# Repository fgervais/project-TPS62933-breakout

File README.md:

#

## Generate gerbers for PCBWay

https://www.pcbway.com/blog/help_center/Generate_Gerber_file_from_Kicad.html

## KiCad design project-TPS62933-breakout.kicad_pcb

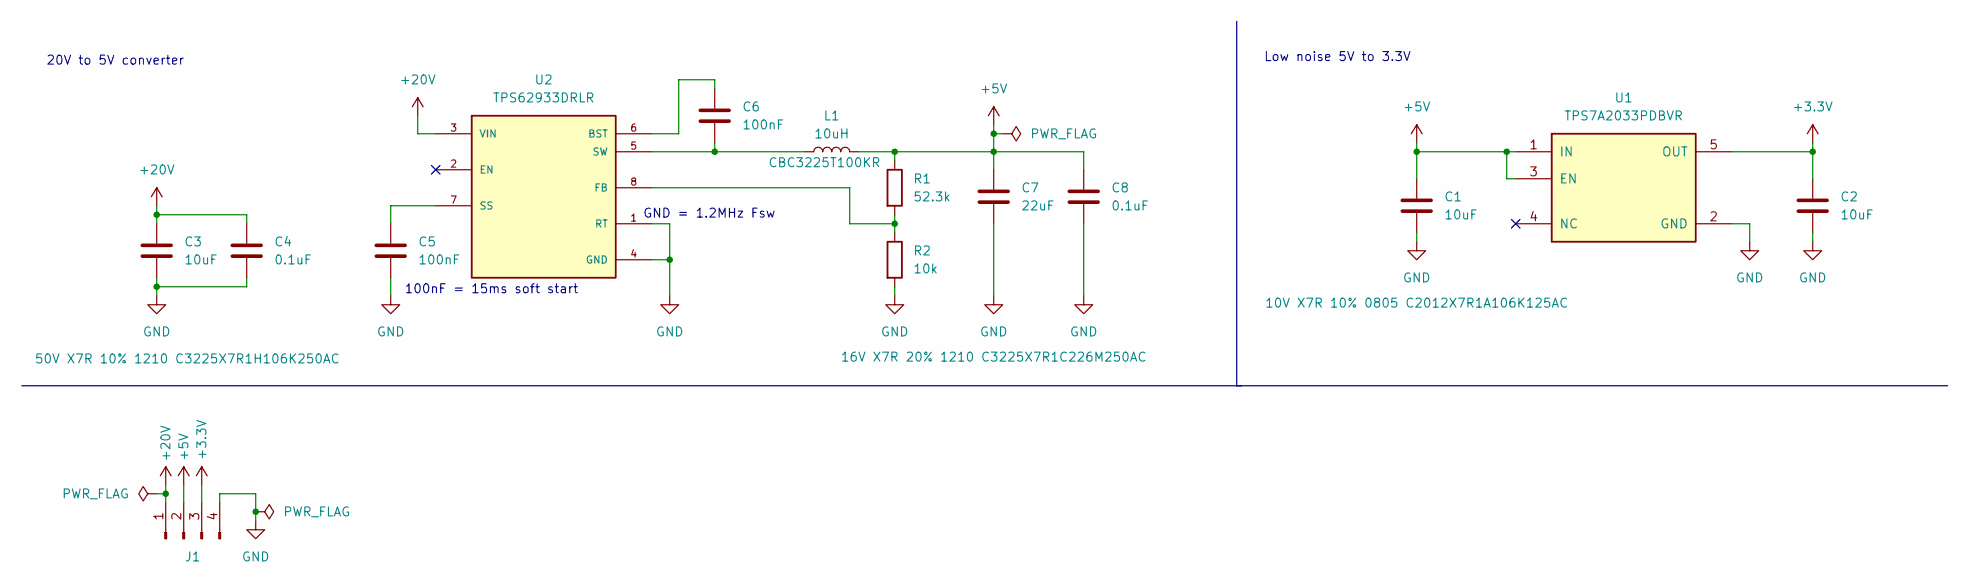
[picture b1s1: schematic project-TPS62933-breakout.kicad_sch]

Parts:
C1, C2: 10uF; C_0805_2012Metric
C3: 10uF; C_1210_3225Metric
C4, C8: 0.1uF; C_0603_1608Metric
C5, C6: 100nF; C_0603_1608Metric
C7: 22uF; C_1210_3225Metric
J1: Conn_01x04_Pin; PinHeader_1x04_P2.54mm_Vertical
L1: 10uH; L_1210_3225Metric
R1: 52.3k; R_0603_1608Metric
R2: 10k; R_0603_1608Metric
U1: TPS7A2033PDBVR
U2: TPS62933DRLR; PARTREV D

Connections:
+3.3V: C2.1, J1.3, U1.5 (OUT)
+5V: C1.1, C7.1, C8.1, J1.2, L1.2, R1.1, U1.1 (IN), U1.3 (EN)
+20V: C3.1, C4.1, J1.1, U2.3 (VIN)
GND: C1.2, C2.2, C3.2, C4.2, C5.2, C7.2, C8.2, J1.4, R2.2, U1.2 (GND), U2.1 (RT), U2.4 (GND)
unnamed: C6.1, U2.6 (BST)
unnamed: R1.2, R2.1, U2.8 (FB)
unnamed: C5.1, U2.7 (SS)
unnamed: C6.2, L1.1, U2.5 (SW)

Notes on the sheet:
100nF = 15ms soft start
Low noise 5V to 3.3V
20V to 5V converter
GND = 1.2MHz Fsw

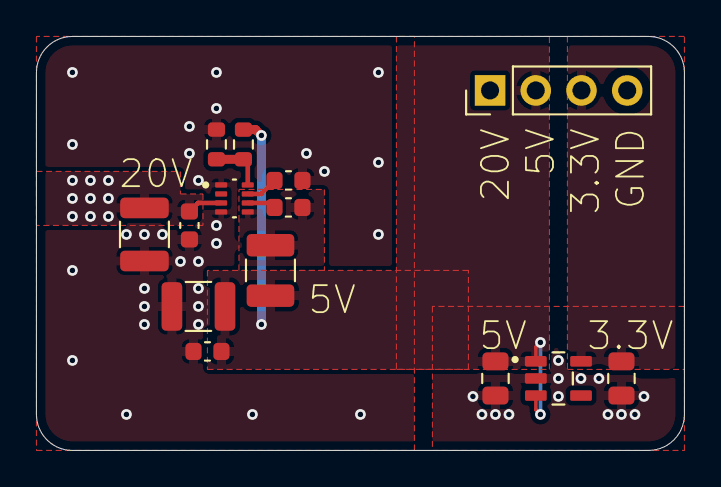
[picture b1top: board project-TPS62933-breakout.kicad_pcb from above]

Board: 4 copper layers, 36.0 x 23.0 mm, 14 parts (0 on the bottom side), 8 nets.

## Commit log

2025-05-12 Add blank kicad project
2025-05-12 Add design
2025-05-12 Add connector silk information
2025-05-12 Add version on silkscreen
2025-05-12 pcb: fix unconnected nets
2025-05-12 pcb: lower clearance on 20V poor
2025-05-12 pcb: update version
2025-05-12 sch: add part information
2025-05-13 pcb: place fab layer
2025-05-20 Generate gerbers
2025-05-20 Add link to gerbers generation instructions
2025-05-21 pcb: fix TPS62933DRLR soldermask too narrow between pads
2025-05-21 Update gerber files
2025-05-30 Add assembly file
